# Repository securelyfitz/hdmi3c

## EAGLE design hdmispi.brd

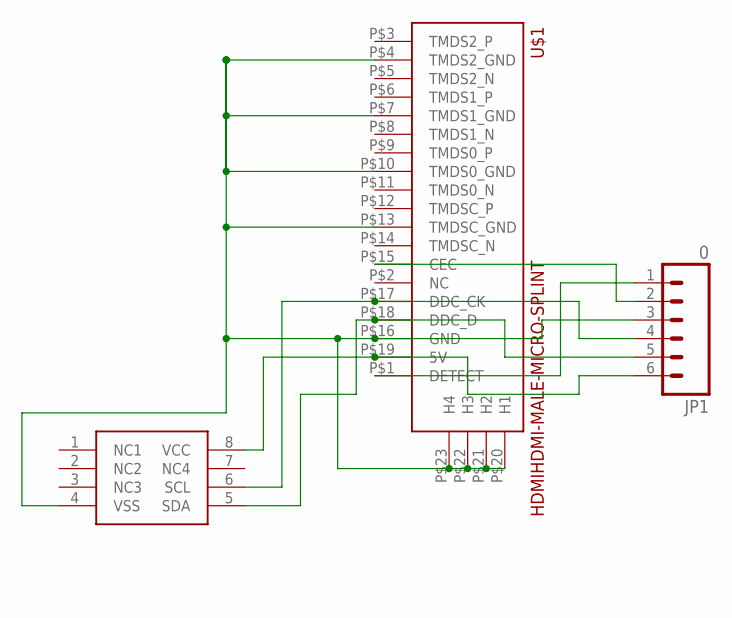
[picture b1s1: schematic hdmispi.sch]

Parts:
JP1: 0; 1X06-SIP_LOCK
U$1: HDMIHDMI-MALE-MICRO-SPLINT; HDMI-MALE-MICRO-SPLINT
U$2: I2CEEPROM-SOIC8; SOIC8

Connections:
5V: JP1.6, U$1.P$19 (5V), U$2.8 (VCC)
DDC_CK: JP1.4, U$1.P$17 (DDC_CK), U$2.6 (SCL)
DDC_D: JP1.5, U$1.P$18 (DDC_D), U$2.5 (SDA)
GND: JP1.3, U$1.P$4 (TMDS2_GND), U$1.P$7 (TMDS1_GND), U$1.P$10 (TMDS0_GND), U$1.P$13 (TMDSC_GND), U$1.P$16 (GND), U$1.P$20 (H1), U$1.P$21 (H2), U$1.P$22 (H3), U$1.P$23 (H4), U$2.4 (VSS)
unnamed: JP1.1, U$1.P$1 (DETECT)
unnamed: JP1.2, U$1.P$15 (CEC)

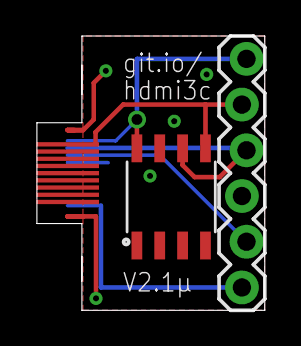
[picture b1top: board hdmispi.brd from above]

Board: 2 copper layers, 12.7 x 15.2 mm, 3 parts (0 on the bottom side), 6 nets.

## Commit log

2016-06-28 work in progress layout of board, does not work.
2016-06-28 next rev of files, v1.0. Switched SDA/SCL wires by accident, doesn't work.
2016-06-28 gerbers for rev 1.0. Still does not work, SDA and SCL swapped
2016-06-28 adding cam rules i normally use. still does not work.
2016-06-28 fixed SDA and SCL swap in library.
2016-06-28 fixed board and schematic with sda/scl corrected.
2016-06-28 updated silkscreen and fixed sda/scl swap. Untested, but should work. rev 1.1
2016-06-28 added component for hdmi splint connector.
2016-06-29 adding readme
2016-06-29 Modified to use a male hdmi splint connector that straddles the edge of the pcb. no longer a full breeakout, only the bare essentials for i2c work
2016-06-30 fixing full pin swizzle on hdmi port. this one should actually work.
2016-06-30 added micro hdmi header and revised board to match. note different pinout!!!

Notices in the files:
parts and their libraries:
SparkFun-Connectors: Licensing: Creative Commons ShareAlike 4.0 International - https://creativecommons.org/licenses/by-sa/4.0
